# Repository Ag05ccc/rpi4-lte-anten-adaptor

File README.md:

# Raspberry Pi 4 LTE çift anten adaptörü

Raspberry Pi 4'ün montaj deliklerine oturan, harici bir LTE modemin iki U.FL anten çıkışını (MAIN ve DIV) iki SMA dişi konnektöre taşıyan pasif kart.

## Durum

Bu kart henüz üretilmedi ve ölçülmedi. Aşağıdakiler yalnızca tasarım araçlarıyla doğrulandı:

- Şema denetimi (ERC): 0 hata, 0 uyarı
- Tasarım kuralı denetimi (DRC): 0 ihlal, 0 bağlanmamış pad
- Şema–kart eşleşmesi: 0 fark

Doğrulanmayanlar:

- 50 Ω hat empedansı formülle hesaplandı (FR4, εr ≈ 4,5, 1,6 mm); simülasyon veya ağ analizörü ölçümü yok.
- Pi 4'e mekanik uyum standart Pi 4 ölçülerine dayanıyor (delikler kenardan 3,5 mm, 49 mm aralık); gerçek kart üzerinde denenmedi. Sipariş öncesi 1:1 çıktı alıp deneyin.

## Özellikler

| | |
|---|---|
| Boyut | 15 × 56 mm, C biçiminde |
| Katman | 2 katman, 1,6 mm FR4 |
| RF hatları | 2 adet, 50 Ω topraklı eş düzlemli hat (1,27 mm iz, 0,2 mm boşluk) |
| Frekans | LTE bantları (700–2700 MHz) için tasarlandı |
| Giriş | 2 × U.FL (J1 = MAIN, J3 = DIV) |
| Çıkış | 2 × kenar montajlı SMA dişi (J2 = MAIN, J4 = DIV) |
| Montaj | 2 × M2.5 delik, Pi 4'ün SD kart tarafındaki kısa kenarı |

İki SMA kartın karşılıklı uçlarında durur; antenler arası mesafe yaklaşık 75 mm olur. C biçimi Pi 4'ün DSI ekran konnektörünü açıkta bırakır.

## Elektriksel bağlantı

Kart tamamen pasiftir; güç veya GPIO bağlantısı yoktur. Toprak, koaksiyel kabloların ekranı üzerinden gelir.

```
LTE modem MAIN (U.FL) ── kablo ── J1 ── R1 (0 Ω) ── J2 (SMA) ── ana anten
LTE modem DIV  (U.FL) ── kablo ── J3 ── R2 (0 Ω) ── J4 (SMA) ── çeşitleme anteni
```

- Modem, U.FL çıkışlı herhangi bir LTE modülü olabilir (USB, mini-PCIe veya M.2). Pi 4'ün kendisinde LTE modem yoktur.
- MAIN anten hem alır hem verir; DIV (bazı modüllerde AUX) yalnızca alır.
- GNSS/GPS çıkışı için üçüncü bir hat yoktur.
- Modemi anten takılı değilken çalıştırmayın.

## Malzeme listesi

| Referans | Parça | Adet | Not |
|---|---|---|---|
| J1, J3 | Hirose U.FL-R-SMT-1 | 2 | U.FL soket |
| J2, J4 | Samtec SMA-J-P-H-ST-EM1 | 2 | 1,6 mm kart için kenar montajlı SMA dişi |
| R1, R2 | 0 Ω, 0603 | 2 | Takılmazsa hat açık devre kalır |
| C1–C4 | 0603 | 0 | Takılmaz; anten uyumlama için boş yer |
| — | U.FL–U.FL kablo, 1,13 mm, 5–15 cm | 2 | Modem ile kart arası |
| — | M2.5 aralayıcı, en az 11 mm | 2 | Kartı GPIO pinlerinin üstünde tutar |
| — | SMA erkek LTE anteni | 2 | |

Başka bir kenar montajlı SMA kullanacaksanız pad ölçülerini footprint ile karşılaştırın.

## Üretim

`rpi4-lte-anten-adaptor-gerber.zip` dosyasını PCB üreticisine yükleyin. Sipariş ayarları: 2 katman, 1,6 mm FR4. Hat empedansı bu kalınlığa göre hesaplandığı için farklı kalınlık seçmeyin.

## Montaj

1. J1, J3 (U.FL), R1, R2 (0 Ω) ve J2, J4 (SMA) parçalarını lehimleyin. SMA'nın orta pini üst yüzdeki orta pad'e, toprak ayakları iki yüzdeki yan pad'lere gelir.
2. Multimetreyle kontrol edin: her SMA'nın orta pini ile kendi U.FL orta pini arasında süreklilik olmalı, orta pin ile toprak arasında kısa devre olmamalı.
3. Kartı iki M2.5 aralayıcıyla Pi 4'ün SD kart tarafındaki kısa kenarına, SMA'lar uzun kenarlara bakacak şekilde takın.
4. U.FL kabloları modemin MAIN ve DIV çıkışlarından J1 ve J3'e bağlayın, antenleri takın.

## Dosyalar

| Dosya | İçerik |
|---|---|
| `rpi4-lte-anten-adaptor.kicad_pro` / `.kicad_sch` / `.kicad_pcb` | KiCad 9 projesi |
| `sema.pdf` | Şema |
| `gerber/` | Gerber ve delik dosyaları |
| `rpi4-lte-anten-adaptor-gerber.zip` | Üreticiye yüklenecek paket |
| `drc-raporu.txt` | DRC raporu |
| `onizleme-ust.png`, `onizleme-alt.png` | Kartın üst ve alt görünümü |

## Wi-Fi sürümü

[`wifi/`](wifi/README.md) klasöründe aynı biçimde, tek hatlı bir kart daha var: Pi 4'ün dahili Wi-Fi/Bluetooth radyosu için 1 × U.FL → 1 × SMA adaptörü. LTE kartından farklı olarak Pi üzerinde lehim değişikliği gerektirir; ayrıntılar ve uyarılar o klasördeki README'de.

## Nasıl tasarlandı

KiCad 9.0.9 ile, [KiCAD-MCP-Server](https://github.com/mixelpixx/KiCAD-MCP-Server) v2.8.3 üzerinden Claude tarafından tasarlandı.

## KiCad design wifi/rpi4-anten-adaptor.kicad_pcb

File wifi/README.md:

# Raspberry Pi 4 Wi-Fi/Bluetooth harici anten adaptörü

Raspberry Pi 4'ün dahili Wi-Fi/Bluetooth radyosunu tek bir kenar montajlı SMA dişi konnektöre taşıyan pasif kart. [LTE kartıyla](../README.md) aynı biçimde ve aynı montaj deliklerinde, tek RF hattıyla.

## Önemli uyarı

Bu kart tek başına yetmez. Pi 4'ün anten çıkışında hazır bir U.FL soket yoktur; sinyali dahili antenden ayırıp bir U.FL sokete yönlendirmek için Pi üzerinde lehim değişikliği gerekir.

- Değişiklik 0201 boyutunda (0,6 × 0,3 mm) bir parça içerir; hata Pi'nin Wi-Fi/Bluetooth'unu kalıcı olarak bozabilir.
- Değişiklik Pi'nin radyo sertifikasını (CE/FCC) geçersiz kılar. Yüksek kazançlı anten yasal yayın gücü sınırını aşabilir.
- Pi tarafındaki adımlar bu projede denenmedi ve doğrulanmadı. Başlamadan önce Pi 4'e özel bir kaynağa bakın, örneğin [element14: External Antenna for Raspberry Pi 4](https://community.element14.com/products/raspberry-pi/b/blog/posts/external-antenna-for-raspberry-pi-4).

## Durum

Bu kart henüz üretilmedi ve ölçülmedi. Yalnızca tasarım araçlarıyla doğrulandı:

- Şema denetimi (ERC): 0 hata, 0 uyarı
- Tasarım kuralı denetimi (DRC): 0 ihlal, 0 bağlanmamış pad
- Şema–kart eşleşmesi: 0 fark

50 Ω hat empedansı formülle hesaplandı (FR4, εr ≈ 4,5, 1,6 mm); simülasyon veya ölçüm yok. Pi 4'e mekanik uyum standart Pi 4 ölçülerine dayanıyor, gerçek kart üzerinde denenmedi.

## Özellikler

| | |
|---|---|
| Boyut | 15 × 56 mm, C biçiminde |
| Katman | 2 katman, 1,6 mm FR4 |
| RF hattı | 1 adet, 50 Ω topraklı eş düzlemli hat (1,27 mm iz, 0,2 mm boşluk), yaklaşık 8 mm |
| Frekans | 2,4 GHz ve 5 GHz Wi-Fi/Bluetooth |
| Giriş | 1 × U.FL (J1, Pi tarafı) |
| Çıkış | 1 × kenar montajlı SMA dişi (J2) |
| Montaj | 2 × M2.5 delik, Pi 4'ün SD kart tarafındaki kısa kenarı |

## Elektriksel bağlantı

```
Pi 4 Wi-Fi çıkışı ── (Pi'ye lehimlenen U.FL) ── kablo ── J1 ── R1 (0 Ω) ── J2 (SMA) ── anten
```

Kart pasiftir; güç veya GPIO bağlantısı yoktur. Bluetooth aynı anteni kullandığı için o da harici antene geçer. Anten takılı değilken Pi'nin Wi-Fi'ını çalıştırmayın.

## Malzeme listesi

| Referans | Parça | Adet | Not |
|---|---|---|---|
| J1 | Hirose U.FL-R-SMT-1 | 1 | U.FL soket |
| J2 | Samtec SMA-J-P-H-ST-EM1 | 1 | 1,6 mm kart için kenar montajlı SMA dişi |
| R1 | 0 Ω, 0603 | 1 | Takılmazsa hat açık devre kalır |
| C1, C2 | 0603 | 0 | Takılmaz; anten uyumlama için boş yer |
| — | U.FL–U.FL kablo, 1,13 mm, 5–10 cm | 1 | Pi ile kart arası |
| — | M2.5 aralayıcı, en az 11 mm | 2 | Kartı GPIO pinlerinin üstünde tutar |
| — | SMA erkek 2,4/5 GHz anten | 1 | Tüketici Wi-Fi antenlerinin çoğu RP-SMA'dır, uymaz |

## Üretim

`rpi4-anten-adaptor-gerber.zip` dosyasını PCB üreticisine yükleyin. Sipariş ayarları: 2 katman, 1,6 mm FR4.

## Dosyalar

| Dosya | İçerik |
|---|---|
| `rpi4-anten-adaptor.kicad_pro` / `.kicad_sch` / `.kicad_pcb` | KiCad 9 projesi |
| `sema.pdf` | Şema |
| `gerber/` | Gerber ve delik dosyaları |
| `rpi4-anten-adaptor-gerber.zip` | Üreticiye yüklenecek paket |
| `drc-raporu.txt` | DRC raporu |
| `onizleme-ust.png`, `onizleme-alt.png` | Kartın üst ve alt görünümü |

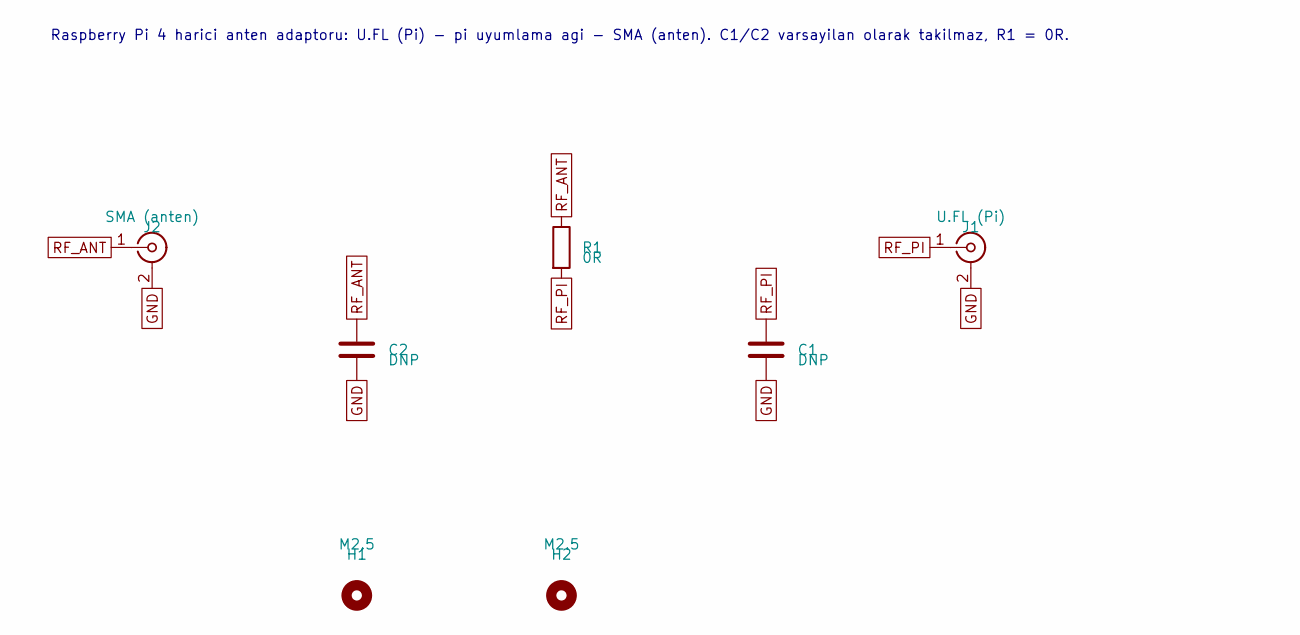
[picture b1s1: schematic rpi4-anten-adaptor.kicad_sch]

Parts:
C1, C2: DNP; C_0603_1608Metric
H1, H2: M2.5; MountingHole_2.7mm_M2.5
J1: U.FL (Pi); U.FL_Hirose_U.FL-R-SMT-1_Vertical
J2: SMA (anten); SMA_Samtec_SMA-J-P-H-ST-EM1_EdgeMount
R1: 0R; R_0603_1608Metric

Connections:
GND: C1.2, C2.2, J1.2 (Ext), J2.2 (Ext)
RF_ANT: C2.1, J2.1 (In), R1.1
RF_PI: C1.1, J1.1 (In), R1.2

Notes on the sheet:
Raspberry Pi 4 harici anten adaptoru: U.FL (Pi) - pi uyumlama agi - SMA (anten). C1/C2 varsayilan olarak takilmaz, R1 = 0R.

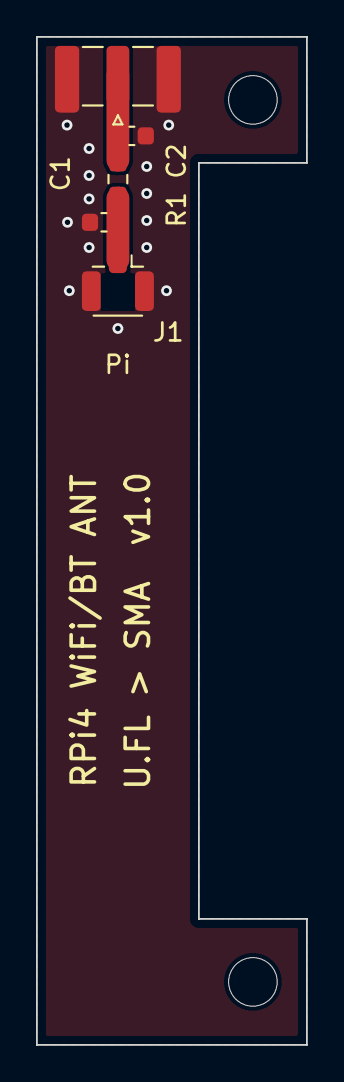
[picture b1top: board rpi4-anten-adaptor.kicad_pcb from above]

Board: 2 copper layers, 15.0 x 56.0 mm, 7 parts (0 on the bottom side), 3 nets.
